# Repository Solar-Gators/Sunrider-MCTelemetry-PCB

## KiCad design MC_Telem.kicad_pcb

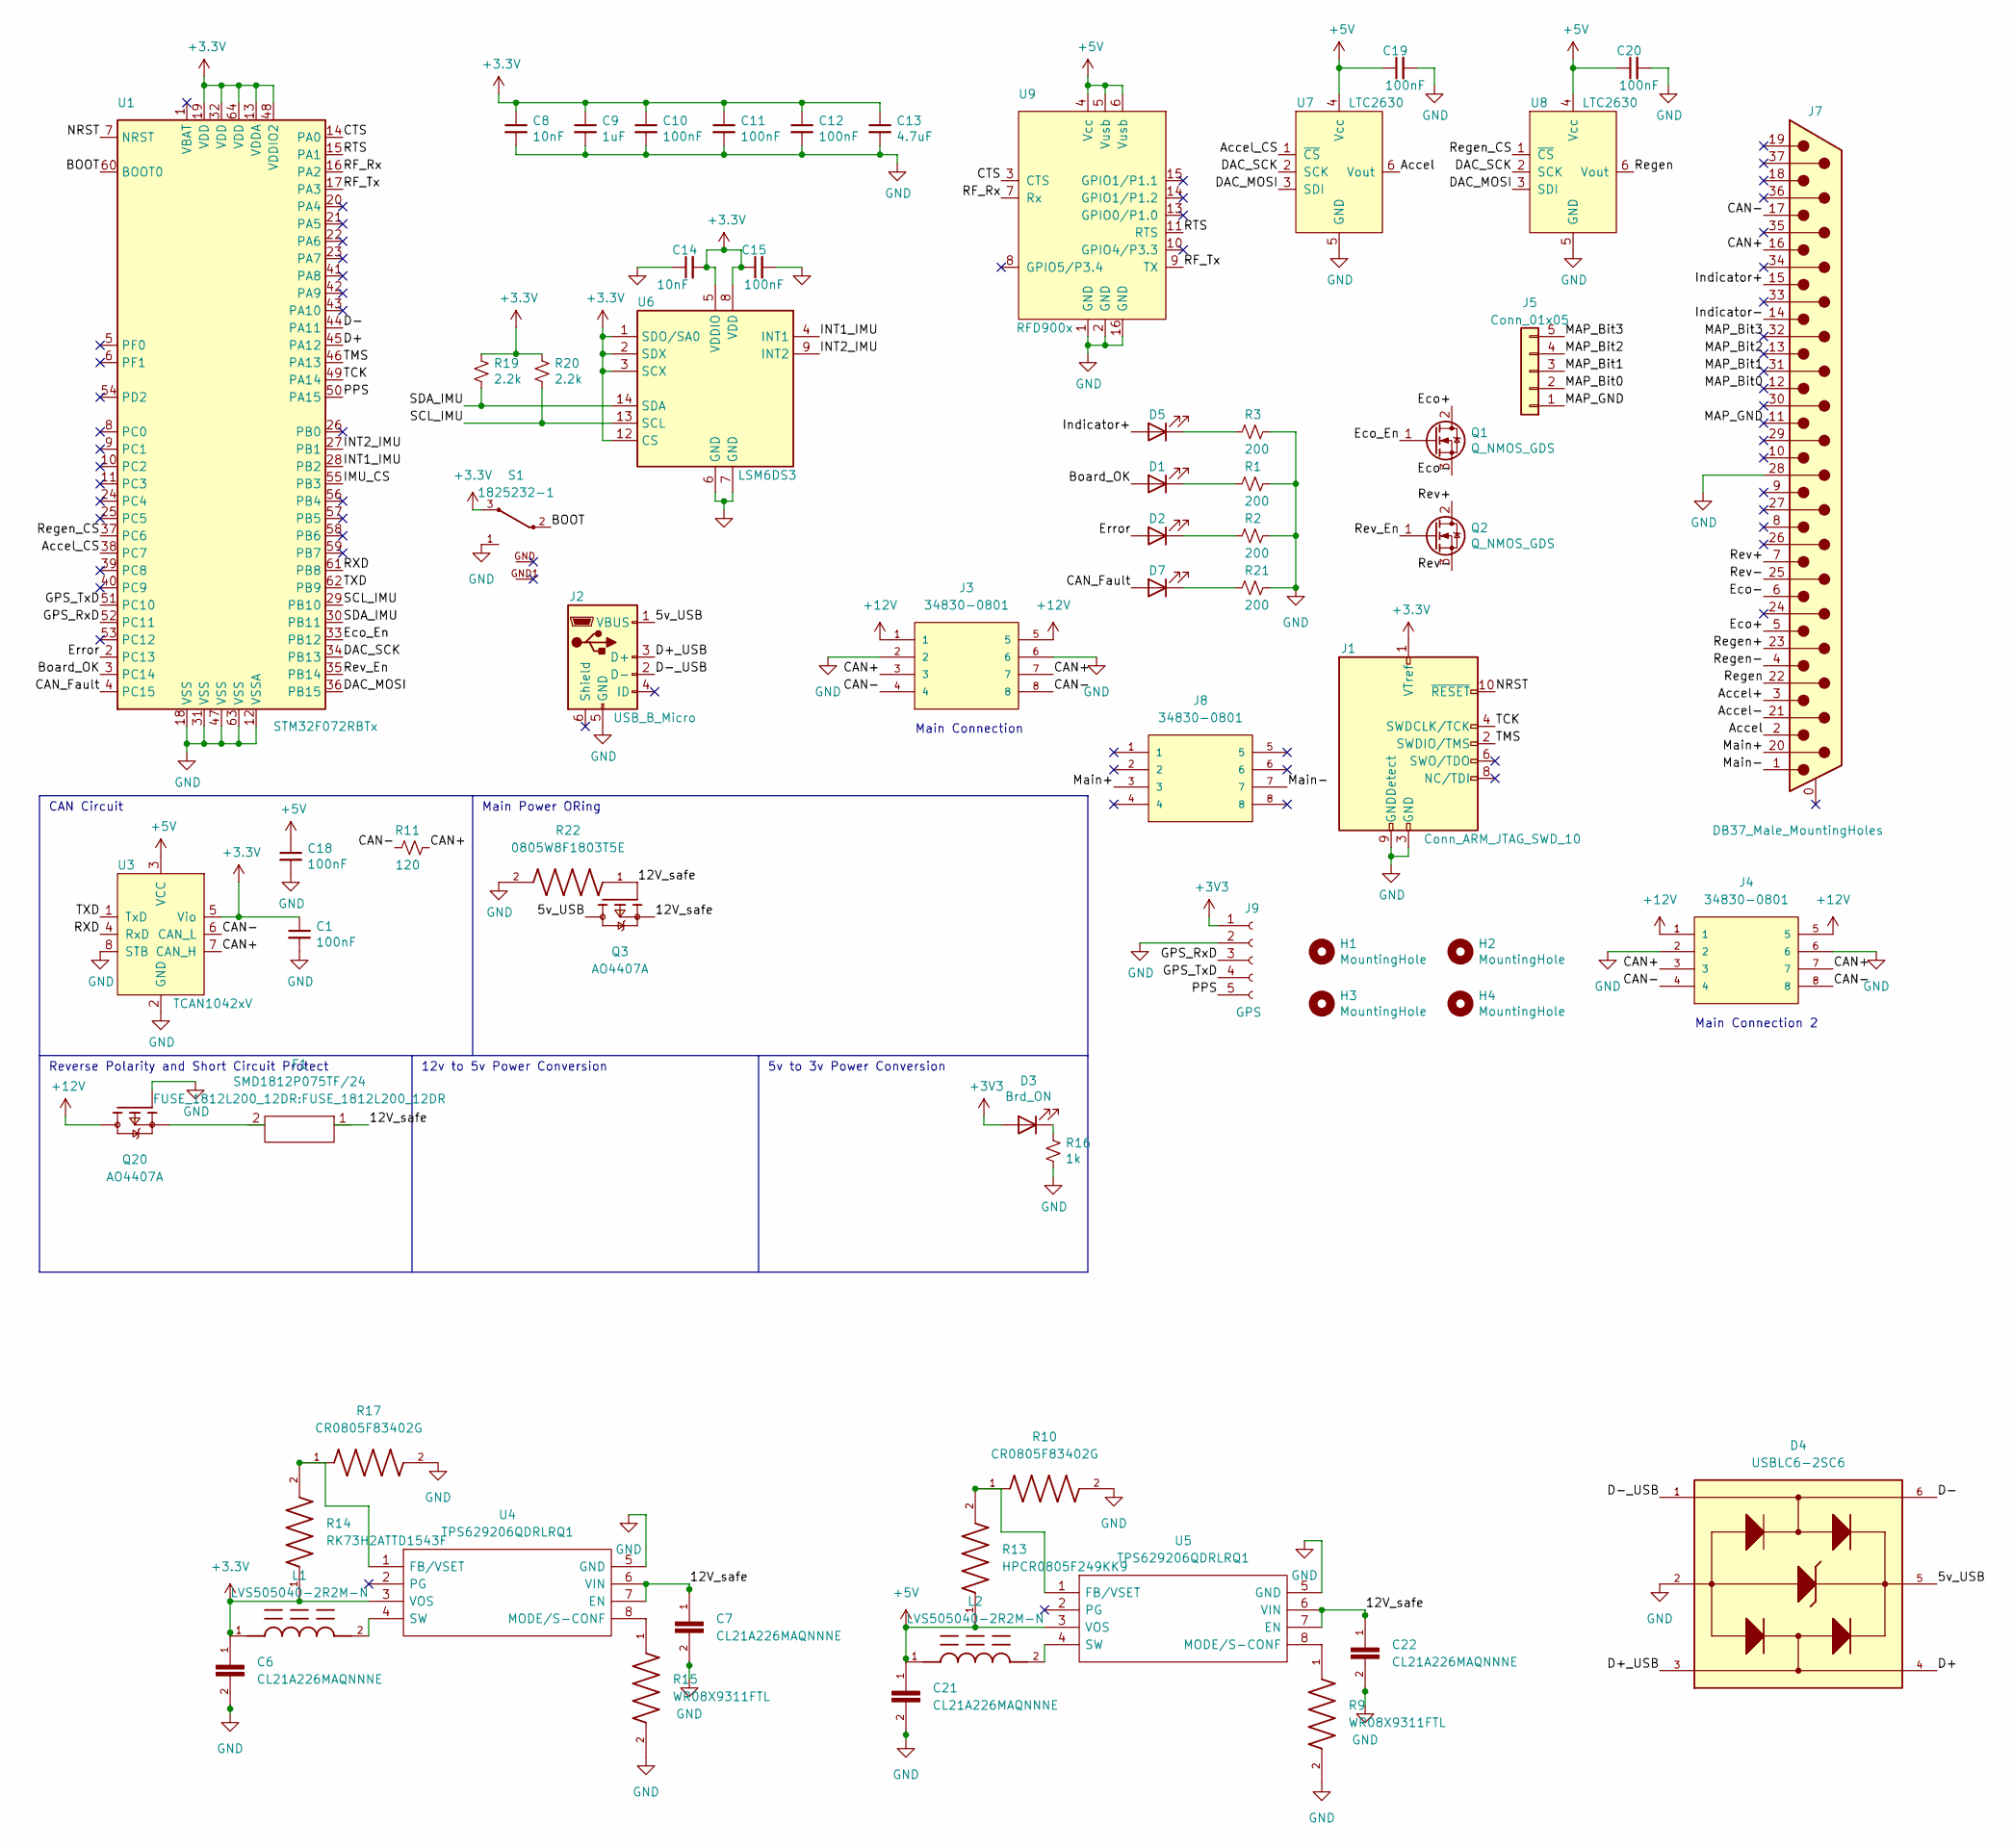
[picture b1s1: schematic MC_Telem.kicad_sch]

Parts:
C1, C10, C11, C12, C15, C18, C19, C20: 100nF; C_0402_1005Metric; LCSC# C307331
C6, C7, C21, C22: CL21A226MAQNNNE; CAPC2012X140N; JLCPCB C45783
C8, C14: 10nF; C_0402_1005Metric; LCSC# C15195
C9: 1uF; C_0402_1005Metric; LCSC# C52923
C13: 4.7uF; C_0402_1005Metric; LCSC# C23733
D1: Board OK; LED_0805_2012Metric; LCSC# C2297
D2: Error; LED_0603_1608Metric; LCSC# C2286
D3: Brd_ON; LED_0805_2012Metric; LCSC# C2297
D4: USBLC6-2SC6; SOT95P280X145-6N; JLCPCB C5180249
D5: Board OK; LED_0805_2012Metric; LCSC# C34499
D7: CAN ERR; LED_0603_1608Metric; LCSC# C2286
F1: SMD1812P075TF/24; FUSE_1812L200_12DR
H1, H2, H3, H4: MountingHole; MountingHole_3.2mm_M3
J1: Conn_ARM_JTAG_SWD_10; PinHeader_2x05_P1.27mm_Vertical_SMD
J2: USB_B_Micro; USB_Micro-B_Molex_47346-0001
J3, J4, J8: 34830-0801; MOLEX_34830-0801; PARTREV A2
J5: Conn_01x05; SolderWire-0.75sqmm_1x05_P4.8mm_D1.25mm_OD2.3mm
J7: DB37_Male_MountingHoles; DSUB-37_Male_Horizontal_P2.77x2.84mm_EdgePinOffset7.70mm_Ho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
J9: GPS; PinSocket_1x05_P2.54mm_Vertical
L1, L2: LVS505040-2R2M-N; IND_SDR0403-2R2ML
Q1, Q2: Q_NMOS_GDS; SOT-23; LCSC# C20917
Q3, Q20: AO4407A; SOIC127P600X175-8N; PARTREV I
R1, R2, R3, R21: 200; R_0603_1608Metric; LCSC# C8218
R9, R15: WR08X9311FTL; RESC2012X60N; JLCPCB C334950
R10, R17: CR0805F83402G; RESC2012X60N; JLCPCB C101673
R11: 120; R_1206_3216Metric_Pad1.30x1.75mm_HandSolder
R13: HPCR0805F249KK9; RESC2012X60N; JLCPCB C365271
R14: RK73H2ATTD1543F; RESC2012X60N; JLCPCB C317465
R16: 1k; R_0603_1608Metric; LCSC# C21190
R19, R20: 2.2k; R_0603_1608Metric; LCSC# C4190
R22: 0805W8F1803T5E; RESC2012X60N; JLCPCB C17501
S1: 1825232-1
U1: STM32F072RBTx; LQFP-64_10x10mm_P0.5mm
U3: TCAN1042xV; SOIC-8
U4, U5: TPS629206QDRLRQ1; SOTFL50P160X60-8N; Mouser Part Number 595-TPS629206QDRLRQ1
U6: LSM6DS3; LGA-14_3x2.5mm_P0.5mm_LayoutBorder3x4y; LCSC# C784817
U7, U8: LTC2630; SOT-363_SC-70-6_Handsoldering
U9: RFD900x

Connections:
+5V: C18.1, C19.1, C20.1, C21.1, L2.1, R13.1, U3.3 (VCC), U5.3 (VOS), U7.4 (Vcc), U8.4 (Vcc), U9.4 (Vcc), U9.5 (Vusb), U9.6 (Vusb)
+12V: J3.1, J3.5, J4.1, J4.5, Q20.5, Q20.6, Q20.7, Q20.8
/5v_USB: D4.5, J2.1 (VBUS), Q3.5, Q3.6, Q3.7, Q3.8
/12V_safe: C7.1, C22.1, F1.1, Q3.1, Q3.2, Q3.3, Q3.4, R22.1, U4.6 (VIN), U4.7 (EN), U5.6 (VIN), U5.7 (EN)
/Accel: J7.2, U7.6 (Vout)
/Accel+: J7.3
/Accel-: J7.21
/Accel_CS: U1.38 (PC7), U7.1 (~CS)
/BOOT: S1.2, U1.60 (BOOT0)
/Board_OK: D1.2 (A), U1.3 (PC14)
/CAN+: J3.3, J3.7, J4.3, J4.7, J7.16, R11.2, U3.7 (CAN_H)
/CAN-: J3.4, J3.8, J4.4, J4.8, J7.17, R11.1, U3.6 (CAN_L)
/CAN_Fault: D7.2 (A), U1.4 (PC15)
/CTS: U1.14 (PA0), U9.3 (CTS)
/D+: D4.4, U1.45 (PA12)
/D+_USB: D4.3, J2.3 (D+)
/D-: D4.6, U1.44 (PA11)
/D-_USB: D4.1, J2.2 (D-)
/DAC_MOSI: U1.36 (PB15), U7.3 (SDI), U8.3 (SDI)
/DAC_SCK: U1.34 (PB13), U7.2 (SCK), U8.2 (SCK)
/Eco+: J7.5, Q1.2 (D)
/Eco-: J7.6, Q1.3 (S)
/Eco_En: Q1.1 (G), U1.33 (PB12)
/Error: D2.2 (A), U1.2 (PC13)
/GPS_RxD: J9.3, U1.52 (PC11)
/GPS_TxD: J9.4, U1.51 (PC10)
/IMU_CS: U1.55 (PB3)
/INT1_IMU: U1.28 (PB2), U6.4 (INT1)
/INT2_IMU: U1.27 (PB1), U6.9 (INT2)
/Indicator+: D5.2 (A), J7.15
/Indicator-: J7.14
/MAP_Bit0: J5.2, J7.12
/MAP_Bit1: J5.3, J7.31
/MAP_Bit2: J5.4, J7.13
/MAP_Bit3: J5.5, J7.32
/MAP_GND: J5.1, J7.11
/Main+: J7.20, J8.3
/Main-: J7.1, J8.7
/NRST: J1.10 (~RESET), U1.7 (NRST)
/PPS: J9.5, U1.50 (PA15)
/RF_Rx: U1.16 (PA2), U9.7 (Rx)
/RF_Tx: U1.17 (PA3), U9.9 (TX)
/RTS: U1.15 (PA1), U9.11 (RTS)
/RXD: U1.61 (PB8), U3.4 (RxD)
/Regen: J7.22, U8.6 (Vout)
/Regen+: J7.23
/Regen-: J7.4
/Regen_CS: U1.37 (PC6), U8.1 (~CS)
/Rev+: J7.7, Q2.2 (D)
/Rev-: J7.25, Q2.3 (S)
/Rev_En: Q2.1 (G), U1.35 (PB14)
/SCL_IMU: R20.2, U1.29 (PB10), U6.13 (SCL)
/SDA_IMU: R19.2, U1.30 (PB11), U6.14 (SDA)
/TCK: J1.4 (SWDCLK/TCK), U1.49 (PA14)
/TMS: J1.2 (SWDIO/TMS), U1.46 (PA13)
/TXD: U1.62 (PB9), U3.1 (TxD)
GND: C1.2, C6.2, C7.2, C8.2, C9.2, C10.2, C11.2, C12.2, C13.2, C14.1, C15.2, C18.2, C19.2, C20.2, C21.2, C22.2, D4.2, J1.3 (GND), J1.5 (GND), J1.9 (GNDDetect), J2.5 (GND), J3.2, J3.6, J4.2, J4.6, J7.28, J9.2, Q20.4, R1.1, R2.1, R3.1, R9.2, R10.2, R15.2, R16.2, R17.2, R21.1, R22.2, S1.1, U1.12 (VSSA), U1.18 (VSS), U1.31 (VSS), U1.47 (VSS), U1.63 (VSS), U3.2 (GND), U3.8 (STB), U4.5 (GND), U5.5 (GND), U6.6 (GND), U6.7 (GND), U7.5 (GND), U8.5 (GND), U9.1 (GND), U9.2 (GND), U9.16 (GND)
unnamed: D1.1 (K), R1.2
unnamed: D2.1 (K), R2.2
unnamed: D3.1 (K), R16.1
unnamed: D5.1 (K), R3.2
unnamed: D7.1 (K), R21.2
unnamed: F1.2, Q20.1, Q20.2, Q20.3
unnamed: L1.2, U4.4 (SW)
unnamed: L2.2, U5.4 (SW)
unnamed: R9.1, U5.8 (MODE/S-CONF)
unnamed: R10.1, R13.2, U5.1 (FB/VSET)
unnamed: R14.2, R17.1, U4.1 (FB/VSET)
unnamed: R15.1, U4.8 (MODE/S-CONF)

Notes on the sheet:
Reverse Polarity and Short Circuit Protect
5v to 3v Power Conversion
Main Connection
CAN Circuit
Main Connection 2
Main Power ORing
12v to 5v Power Conversion

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
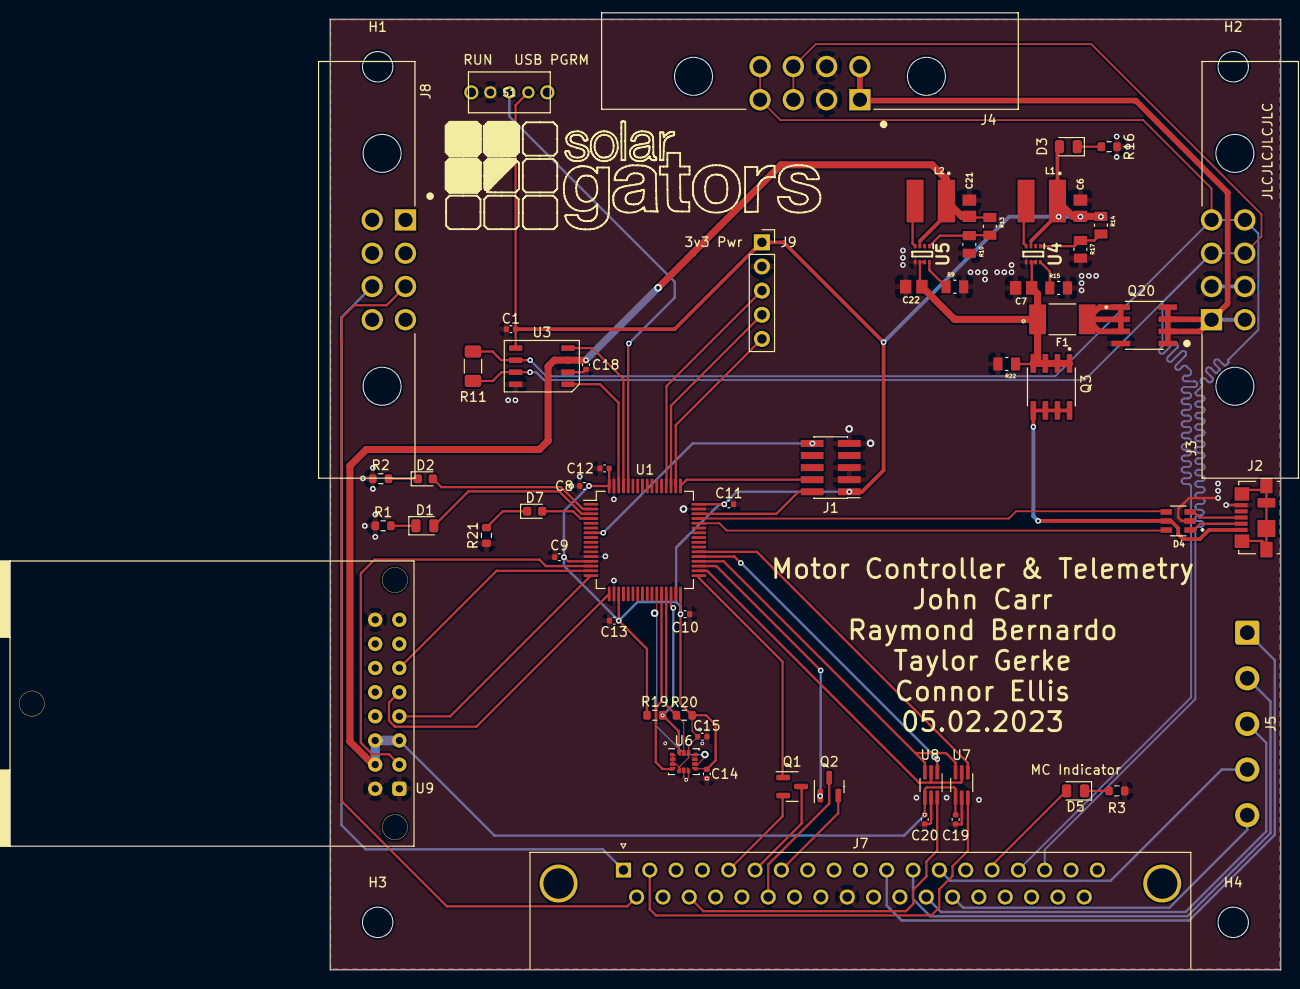
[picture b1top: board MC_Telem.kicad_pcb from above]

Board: 2 copper layers, 100.0 x 100.0 mm, 65 parts (0 on the bottom side), 64 nets.

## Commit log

2023-01-31 Initial Commit
    Known Issues
    5V LDO ADJ pin must be grounded
    5V power mux does not work and must be replaced
2023-09-11 FSGP MC Telemetry Hardware
    Final PCB revision used for Sunrider at FSGP 2023
